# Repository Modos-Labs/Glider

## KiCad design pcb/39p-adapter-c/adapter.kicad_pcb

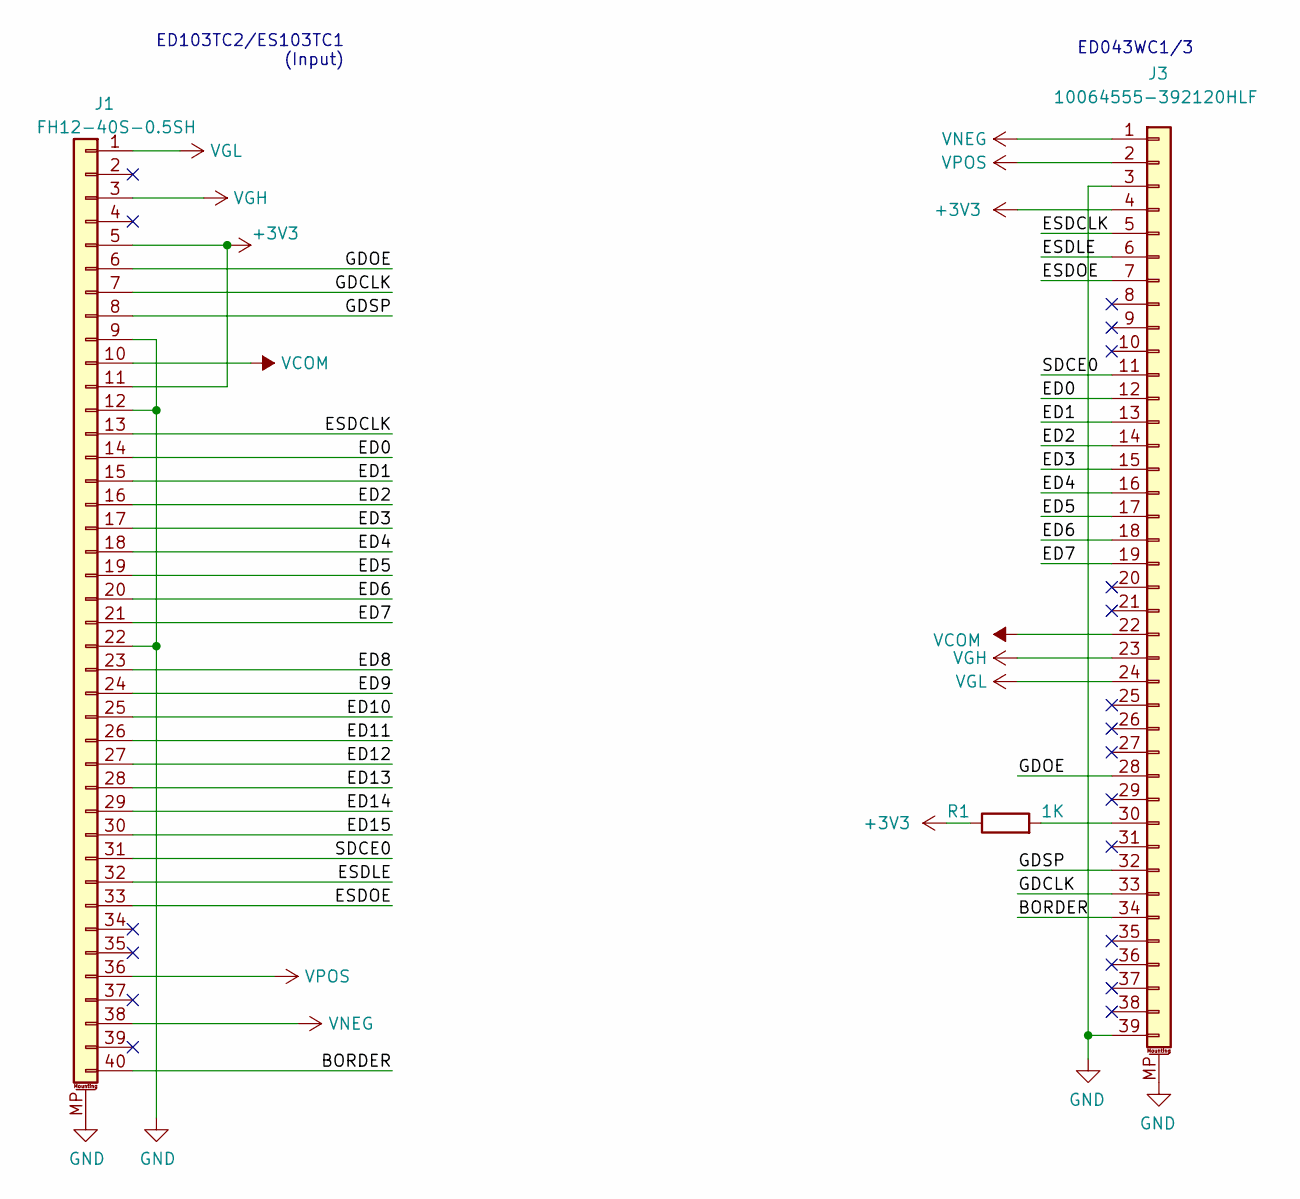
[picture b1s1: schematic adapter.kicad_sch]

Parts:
J1: FH12-40S-0.5SH; Hirose_FH12-40S-0.5SH_1x40-1MP_P0.50mm_Horizontal_Reversed
J3: 10064555-392120HLF; HRS_FH26W-39S-0.3SHW(60); LCSC 609-10064555-392120HLFCT-ND
R1: 1K; R_0603_1608Metric

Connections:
+3V3: J1.5, J1.11, J3.4, R1.1
/BORDER: J1.40, J3.34
/ED0: J1.14, J3.12
/ED1: J1.15, J3.13
/ED2: J1.16, J3.14
/ED3: J1.17, J3.15
/ED4: J1.18, J3.16
/ED5: J1.19, J3.17
/ED6: J1.20, J3.18
/ED7: J1.21, J3.19
/ED8: J1.23
/ED9: J1.24
/ED10: J1.25
/ED11: J1.26
/ED12: J1.27
/ED13: J1.28
/ED14: J1.29
/ED15: J1.30
/ESDCLK: J1.13, J3.5
/ESDLE: J1.32, J3.6
/ESDOE: J1.33, J3.7
/GDCLK: J1.7, J3.33
/GDOE: J1.6, J3.28
/GDSP: J1.8, J3.32
/SDCE0: J1.31, J3.11
GND: J1.9, J1.12, J1.22, J1.MP (MountPin), J3.3, J3.39, J3.MP (MountPin)
unnamed: J3.30, R1.2
VCOM: J1.10, J3.22
VGH: J1.3, J3.23
VGL: J1.1, J3.24
VNEG: J1.38, J3.1
VPOS: J1.36, J3.2

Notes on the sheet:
ED103TC2/ES103TC1 (Input)
ED043WC1/3

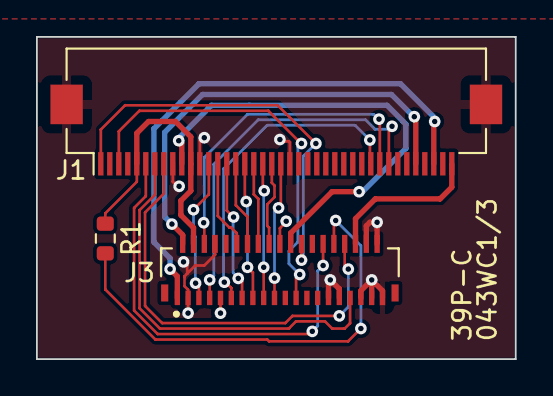
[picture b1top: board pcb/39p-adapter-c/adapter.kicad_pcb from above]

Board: 2 copper layers, 26.6 x 17.9 mm, 3 parts (0 on the bottom side), 24 nets.

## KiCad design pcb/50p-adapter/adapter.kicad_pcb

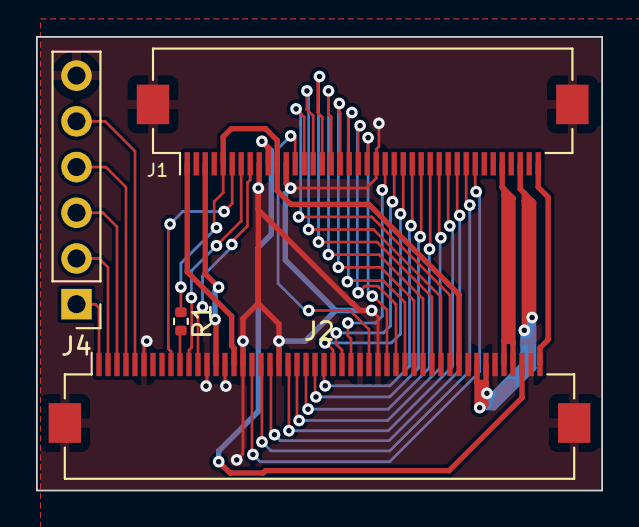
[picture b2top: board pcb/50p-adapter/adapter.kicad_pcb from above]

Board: 2 copper layers, 31.4 x 25.2 mm, 4 parts (0 on the bottom side), 37 nets.

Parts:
J1: FH12-40S-0.5SH; Hirose_FH12-40S-0.5SH_1x40-1MP_P0.50mm_Horizontal_Reversed
J2: FH28-50S-0.5SH; Hirose_FH12-50S-0.5SH_1x50-1MP_P0.50mm_Horizontal
J4: DNP; PinHeader_1x06_P2.54mm_Vertical
R1: 10K; R_0402_1005Metric

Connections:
+3V3: J1.5, J1.11, J2.41, R1.1
/BORDER: J1.40, J2.50
/ED0: J1.14, J2.40
/ED1: J1.15, J2.39
/ED2: J1.16, J2.38
/ED3: J1.17, J2.37
/ED4: J1.18, J2.36
/ED5: J1.19, J2.35
/ED6: J1.20, J2.34
/ED7: J1.21, J2.33
/ED8: J1.23, J2.29
/ED9: J1.24, J2.28
/ED10: J1.25, J2.27
/ED11: J1.26, J2.26
/ED12: J1.27, J2.25
/ED13: J1.28, J2.24
/ED14: J1.29, J2.23
/ED15: J1.30, J2.22
/ESDCLK: J1.13, J2.31
/ESDLE: J1.32, J2.19
/ESDOE: J1.33, J2.18
/GDCLK: J1.7, J2.11
/GDOE: J1.6, J2.9
/GDSP: J1.8, J2.12
/SDCE0: J1.31, J2.20
/SPI_MISO: J2.1, J4.1
/SPI_MOSI: J2.2, J4.2
/SPI_NCS: J2.3, J4.3
/SPI_SCLK: J2.4, J4.4
/SPI_VDD: J2.5, J4.5
GND: J1.9, J1.12, J1.22, J1.MP (MountPin), J2.6, J2.13, J2.15, J2.17, J2.21, J2.30, J2.32, J2.42, J2.45, J2.49, J2.MP (MountPin), J4.6
unnamed: J2.10, R1.2
VCOM: J1.10, J2.48
VGH: J1.3, J2.14
VGL: J1.1, J2.16
VNEG: J1.38, J2.43, J2.44
VPOS: J1.36, J2.46, J2.47
